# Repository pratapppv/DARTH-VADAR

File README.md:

# DARTH-VADAR
A simple ISM Band FMCW RADAR. The writeup can be found [here](https://pratapppv.github.io/DARTH-VADAR/)

Note: The pre-exported Gerber files donot contain etched copper power rail indicators.

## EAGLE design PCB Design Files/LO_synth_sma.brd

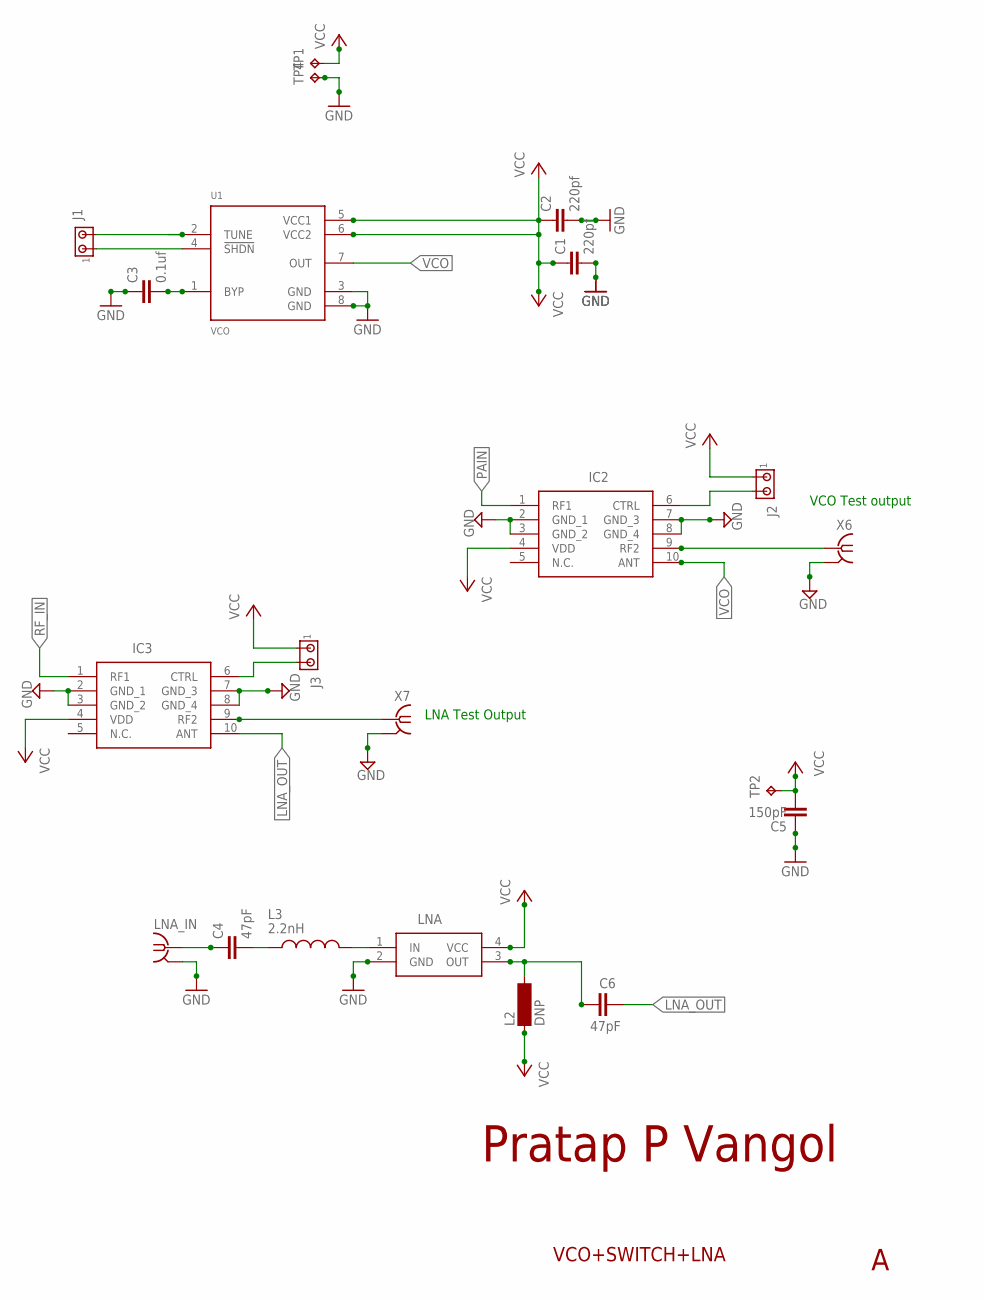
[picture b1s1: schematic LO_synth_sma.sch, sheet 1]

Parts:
C1, C2: 220pf; C0805
C3: 0.1uf; C0805
C4, C6: 47pF; C0805K
C5: 150pF; C0805K
IC2, IC3: BGS12PN10E6327XTSA1; BGSA11GN10E6327XTSA1
J1, J2, J3: MTA02-100; 10X02MTA
L2: DNP; MS85
L3: 2.2nH; INDC2012X103N
LNA: BGA622H6820XTSA1
LNA_IN: SMA-142-0711-821/826; J502-ND-142-0711-821/826
TP1, TP2, TP4: TPPAD1-13; P1-13
U1: VCO; SOP65P490X110-8N
X6: VCO Test; J502-ND-142-0711-821/826
X7: SMA-142-0711-821/826; J502-ND-142-0711-821/826

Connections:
GND: C1.2, C2.2, C3.1, C5.1, IC2.2 (GND_1), IC2.3 (GND_2), IC2.7 (GND_3), IC2.8 (GND_4), IC3.2 (GND_1), IC3.3 (GND_2), IC3.7 (GND_3), IC3.8 (GND_4), LNA.2 (GND), LNA_IN.G@1 (2), LNA_IN.G@2 (2), LNA_IN.G@3 (2), LNA_IN.G@4 (2), TP4.TP, U1.3 (GND), U1.8 (GND), X6.G@1 (2), X6.G@2 (2), X6.G@3 (2), X6.G@4 (2), X7.G@1 (2), X7.G@2 (2), X7.G@3 (2), X7.G@4 (2); also elsewhere on the board
LNA_OUT: C6.2, IC3.10 (ANT)
unnamed: C4.2, L3.1
unnamed: C3.2, U1.1 (BYP)
unnamed: L3.2, LNA.1 (IN)
unnamed: J1.2, U1.2 (TUNE)
unnamed: J1.1, U1.4 (!SHDN)
unnamed: C4.1, LNA_IN.1
unnamed: IC3.9 (RF2), X7.1
unnamed: C6.1, L2.2, LNA.3 (OUT)
unnamed: IC2.6 (CTRL), J2.2
unnamed: IC2.9 (RF2), X6.1
unnamed: IC3.6 (CTRL), J3.2
PAIN: IC2.1 (RF1); also elsewhere on the board
RF_IN: IC3.1 (RF1); also elsewhere on the board
VCC: C1.1, C2.1, C5.2, IC2.4 (VDD), IC3.4 (VDD), J2.1, J3.1, L2.1, LNA.4 (VCC), TP1.TP, TP2.TP, U1.5 (VCC1), U1.6 (VCC2); also elsewhere on the board
VCO: IC2.10 (ANT), U1.7 (OUT)

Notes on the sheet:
Pratap P Vangol
VCO Test output
LNA Test Output
VCO+SWITCH+LNA

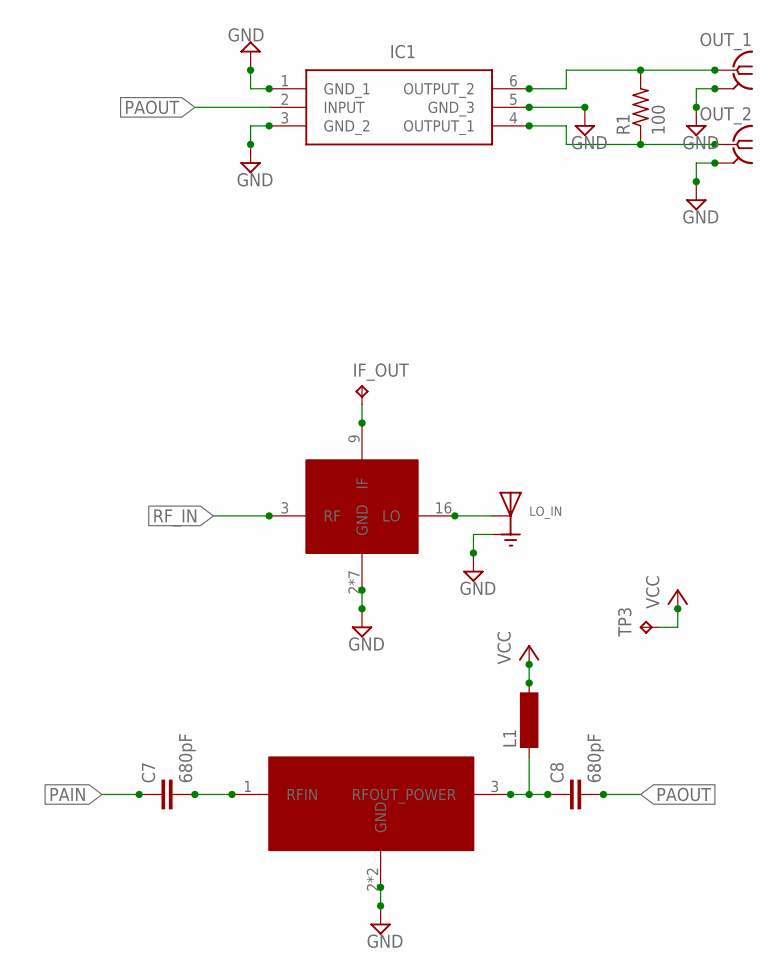
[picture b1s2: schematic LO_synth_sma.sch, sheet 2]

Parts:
C7, C8: 680pF; C0805K
IC1: PD2425J5050S2HF
IF_OUT: TPPAD1-13; P1-13
L1: MS85
LO_IN: U.FL-R-SMT-1(10); HRS_U.FL-R-SMT-1(10)
OUT_1, OUT_2: SMA-142-0711-821/826; J502-ND-142-0711-821/826
R1: 100; R0603
TP3: TPPAD1-13; P1-13
U$1: MDB-73H+QFN-24; QFN24
U$2: GVA-60+; SOT89

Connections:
GND: IC1.1 (GND_1), IC1.3 (GND_2), IC1.5 (GND_3), LO_IN.1 (GND), LO_IN.3 (GND), OUT_1.G@1 (2), OUT_1.G@2 (2), OUT_1.G@3 (2), OUT_1.G@4 (2), OUT_2.G@1 (2), OUT_2.G@2 (2), OUT_2.G@3 (2), OUT_2.G@4 (2), U$1.2 (GND), U$1.4 (GND), U$1.8 (GND), U$1.10 (GND), U$1.15 (GND), U$1.17 (GND), U$1.PD (GND), U$2.2 (GND), U$2.2@1 (GND); also elsewhere on the board
LO: LO_IN.2 (SIG), U$1.16 (LO)
unnamed: IF_OUT.TP, U$1.9 (IF)
unnamed: C7.2, U$2.1 (RFIN)
unnamed: C8.1, L1.1, U$2.3 (RFOUT_POWER)
unnamed: IC1.6 (OUTPUT_2), OUT_1.1, R1.2
unnamed: IC1.4 (OUTPUT_1), OUT_2.1, R1.1
PAIN: C7.1; also elsewhere on the board
PAOUT: C8.2, IC1.2 (INPUT)
RF_IN: U$1.3 (RF); also elsewhere on the board
VCC: L1.2, TP3.TP; also elsewhere on the board

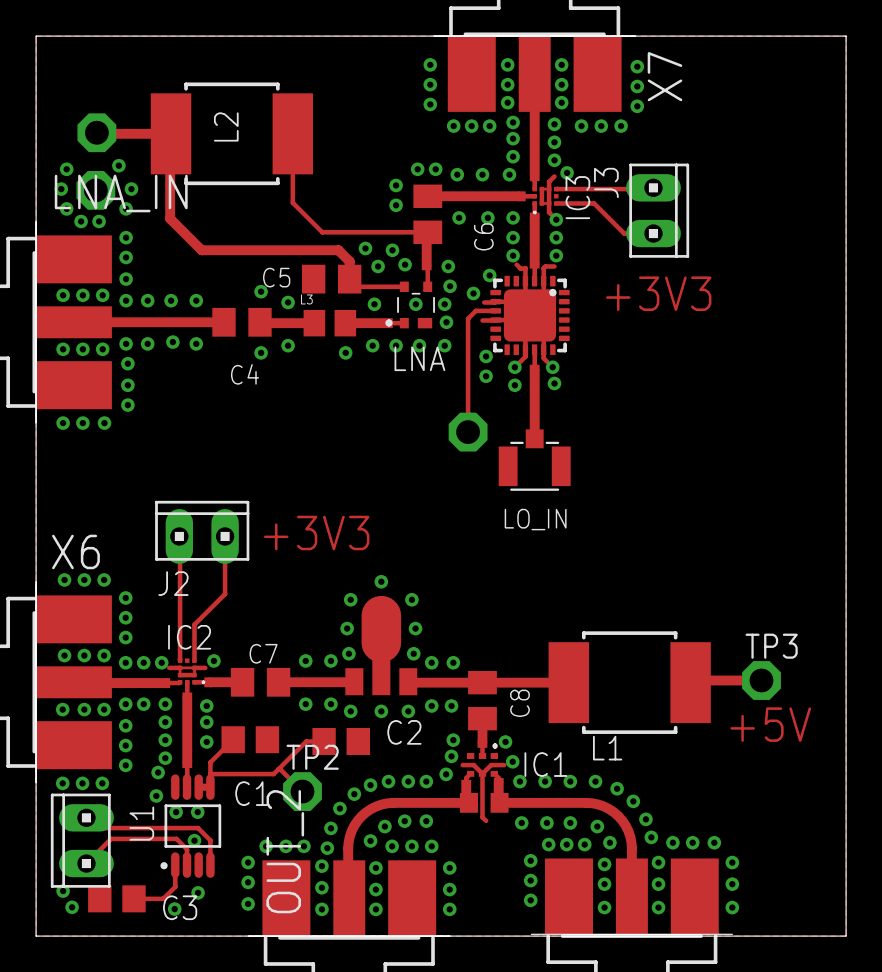
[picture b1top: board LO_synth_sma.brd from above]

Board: 2 copper layers, 45.0 x 50.0 mm, 33 parts (0 on the bottom side), 24 nets.

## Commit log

2021-06-27 Removed Logo HTML
